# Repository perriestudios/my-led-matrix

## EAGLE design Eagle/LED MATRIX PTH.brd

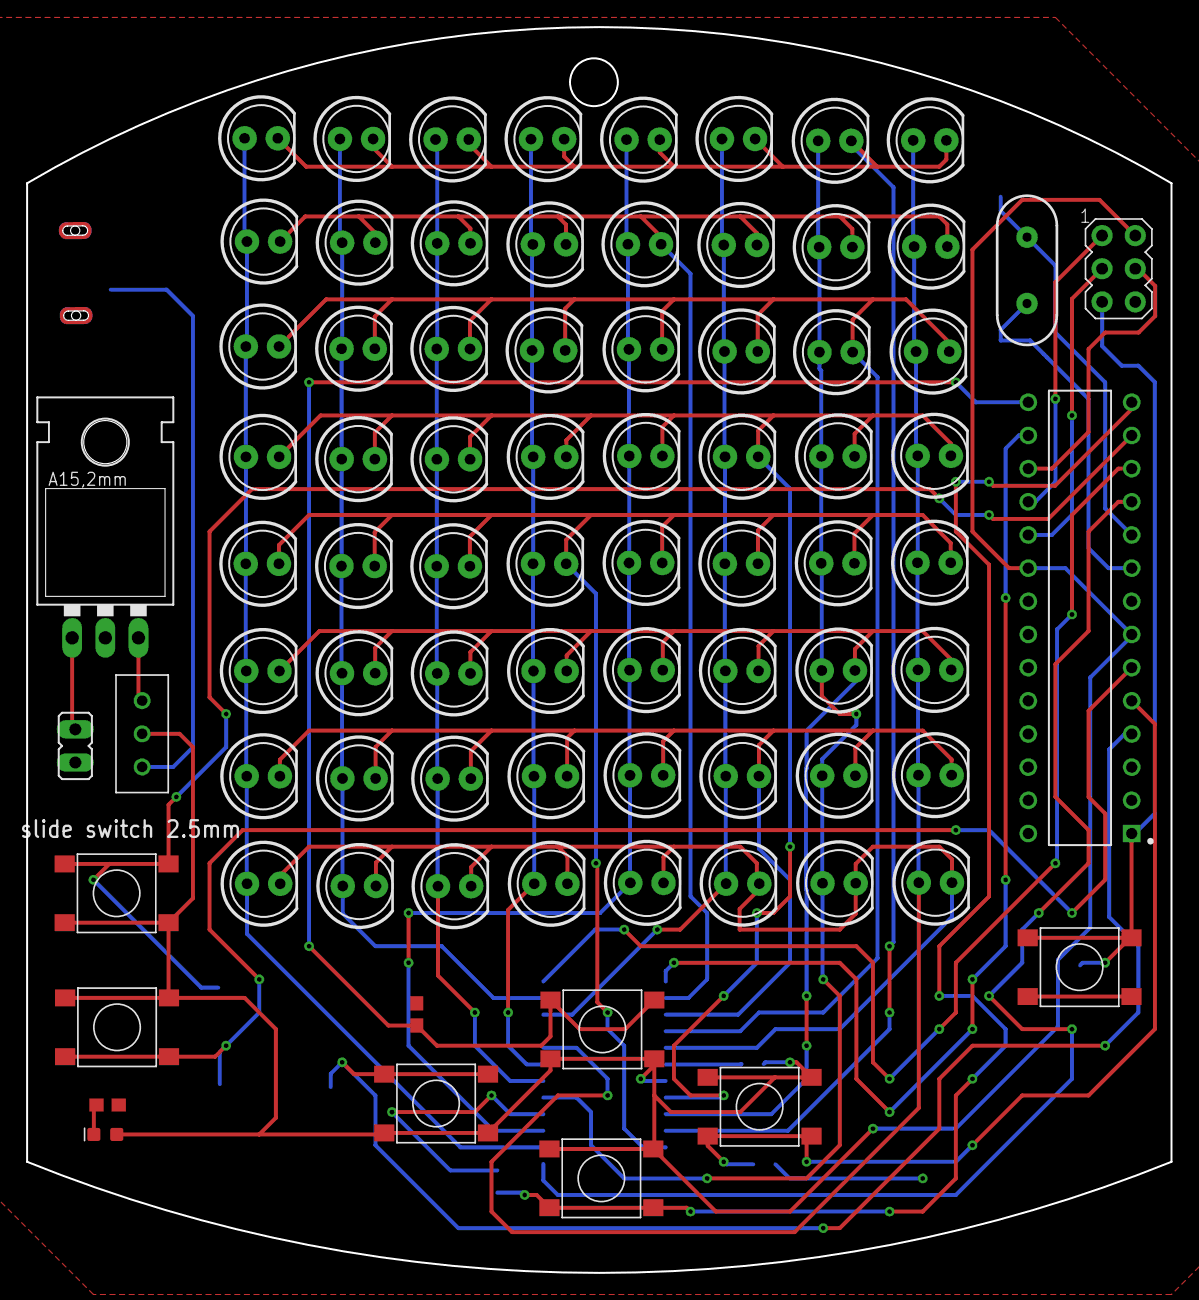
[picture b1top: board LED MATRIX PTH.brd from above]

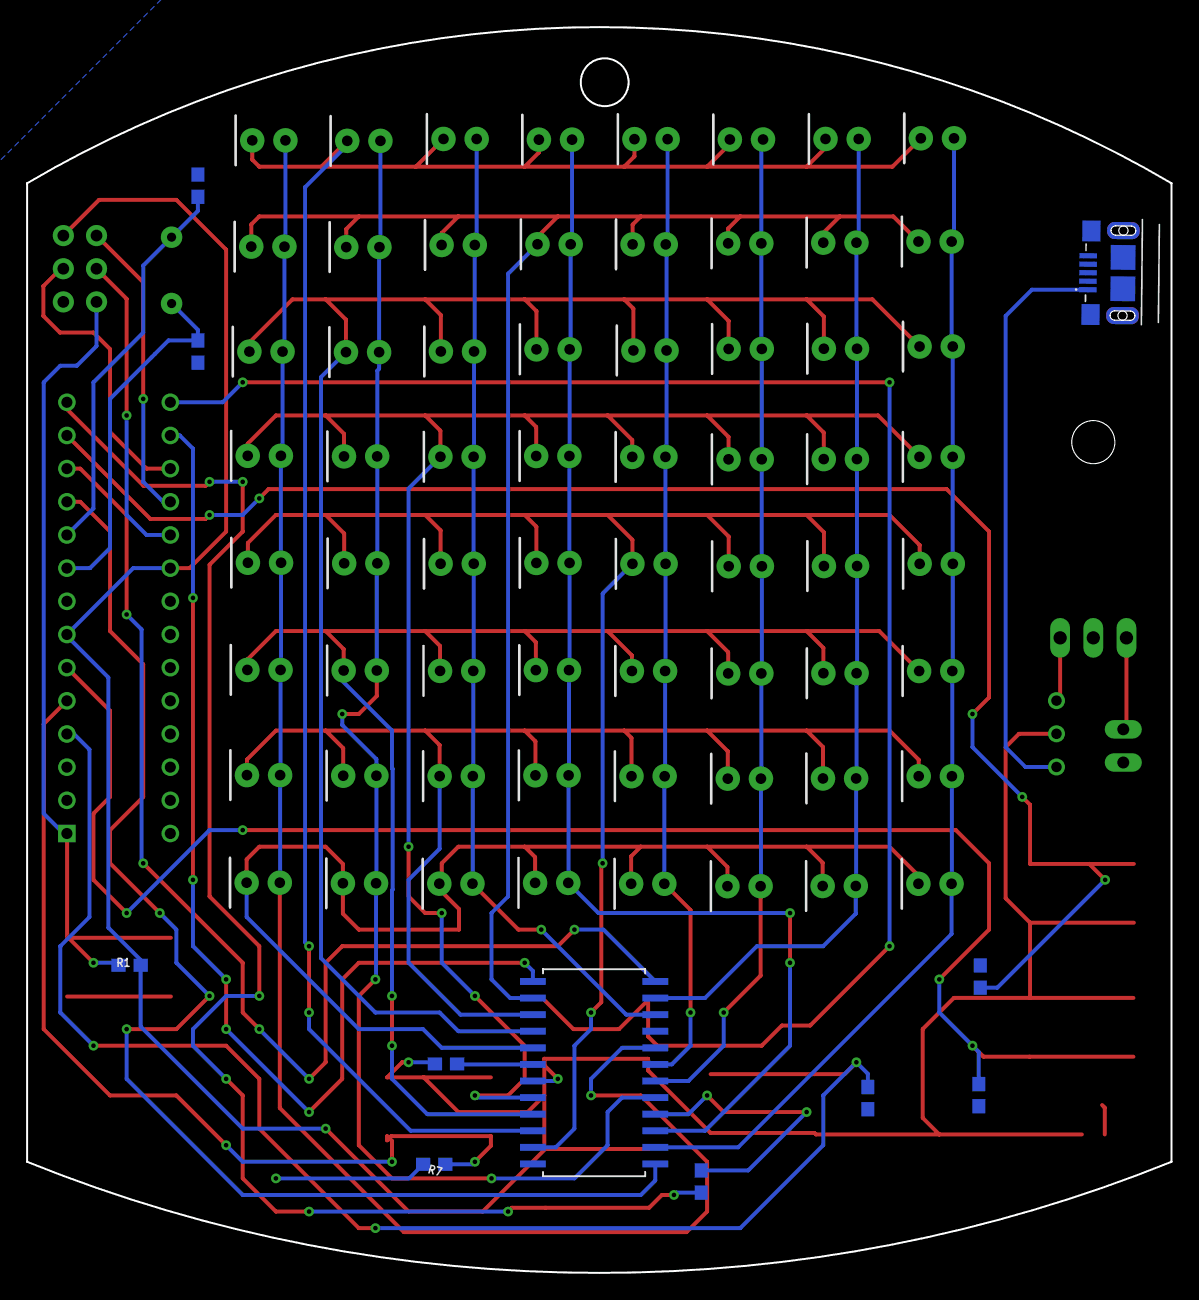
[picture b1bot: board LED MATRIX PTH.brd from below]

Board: 2 copper layers, 87.6 x 95.4 mm, 91 parts (11 on the bottom side), 38 nets.

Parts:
C1, C2: 22pF; 0603
D1: WHITE; LED-0603
D2, D3, D4, D5, D6, D7, D8, D9, D10, D11, D12, D13, D14, D15, D16, D17, D18, D19, D20, D21, D22, D23, D24, D25, D26, D27, D28, D29, D30, D31, D32, D33, D34, D35, D36, D37, D38, D39, D40, D41, D42, D43, D44, D45, D46, D47, D48, D49, D50, D51, D52, D53, D54, D55, D56, D57, D58, D59, D60, D61, D62, D63, D64, D65: LED_5MM
ISP1: AVRISP-6; AVRISP
J2: 2013499-1; TE_2013499-1
JP1: JP1
R1: 10k; 0603
R2: 330; 0603
R3: 22K; 0603
R4, R5, R6, R7, R8, R9: 10K; 0603
S1, S9, S10, S11, S12, S13, S14: PTS645SM43SMTR
U1: 78XXL
U2: ATMEGA328P-PU; DIP794W46P254L2967H457Q28B
U3: MAX7219CWGT; 21-0042B_24
U$1: TS02_SWITCH
Y1: 16MHz; HC49US

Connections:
5V: D1.A, ISP1.2, R1.2, R3.1, S1.3, S1.4, S9.3, S9.4, S10.3, S10.4, S11.3, S11.4, S12.3, S12.4, S13.3, S13.4, U2.7, U2.20, U3.19, U$1.PIN2
5V_BAT: U1.OUT, U$1.PIN3
5V_USB: J2.1, U$1.PIN1
ABC: R8.1, S12.1, S12.2, U2.6
CLK: U2.16, U3.13
COLUMN1: D2.A, D10.A, D18.A, D26.A, D34.A, D42.A, D50.A, D58.A, U3.2
COLUMN2: D3.A, D11.A, D19.A, D27.A, D35.A, D43.A, D51.A, D59.A, U3.11
COLUMN3: D4.A, D12.A, D20.A, D28.A, D36.A, D44.A, D52.A, D60.A, U3.6
COLUMN4: D5.A, D13.A, D21.A, D29.A, D37.A, D45.A, D53.A, D61.A, U3.7
COLUMN5: D6.A, D14.A, D22.A, D30.A, D38.A, D46.A, D54.A, D62.A, U3.3
COLUMN6: D7.A, D15.A, D23.A, D31.A, D39.A, D47.A, D55.A, D63.A, U3.10
COLUMN7: D8.A, D16.A, D24.A, D32.A, D40.A, D48.A, D56.A, D64.A, U3.5
COLUMN8: D9.A, D17.A, D25.A, D33.A, D41.A, D49.A, D57.A, D65.A, U3.8
DEF: R9.1, S13.1, S13.2, U2.13
DIN: U2.11, U3.1
DOWN: R5.1, S9.1, S9.2, U2.14
GND: C1.1, C2.1, ISP1.6, J2.5, JP1.1, R2.1, R4.2, R5.2, R6.2, R7.2, R8.2, R9.2, S14.1, S14.2, U1.GND, U2.8, U2.22, U3.4, U3.9
LEFT: R6.1, S10.1, S10.2, U2.4
LOAD: U2.12, U3.12
MISO: ISP1.1, U2.18
MOSI: ISP1.4, U2.17
unnamed: C1.2, U2.9, Y1.2
unnamed: C2.2, U2.10, Y1.1
unnamed: D1.C, R2.2
unnamed: R3.2, U3.18
RESET: ISP1.5, R1.1, S14.3, S14.4, U2.1
RIGHT: R7.1, S11.1, S11.2, U2.5
ROW1: D2.K, D3.K, D4.K, D5.K, D6.K, D7.K, D8.K, D9.K, U3.22
ROW2: D10.K, D11.K, D12.K, D13.K, D14.K, D15.K, D16.K, D17.K, U3.14
ROW3: D18.K, D19.K, D20.K, D21.K, D22.K, D23.K, D24.K, D25.K, U3.16
ROW4: D26.K, D27.K, D28.K, D29.K, D30.K, D31.K, D32.K, D33.K, U3.20
ROW5: D34.K, D35.K, D36.K, D37.K, D38.K, D39.K, D40.K, D41.K, U3.23
ROW6: D42.K, D43.K, D44.K, D45.K, D46.K, D47.K, D48.K, D49.K, U3.21
ROW7: D50.K, D51.K, D52.K, D53.K, D54.K, D55.K, D56.K, D57.K, U3.15
ROW8: D58.K, D59.K, D60.K, D61.K, D62.K, D63.K, D64.K, D65.K, U3.17
SCK: ISP1.3, U2.19
UP: R4.1, S1.1, S1.2, U2.15
V_BAT: JP1.2, U1.IN

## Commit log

2020-11-17 Added Eagle CAD files
2020-11-17 Added PCB Design Files
2020-11-17 Changed folder name
2020-11-17 Added Gerbers and modified schematic

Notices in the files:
parts and their libraries:
SparkFun-Capacitors: Licensing: Creative Commons ShareAlike 4.0 International - https://creativecommons.org/licenses/by-sa/4.0
